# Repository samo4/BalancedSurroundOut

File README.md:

# BalancedSurroundOut

I2S balanced +4dBu DAC.

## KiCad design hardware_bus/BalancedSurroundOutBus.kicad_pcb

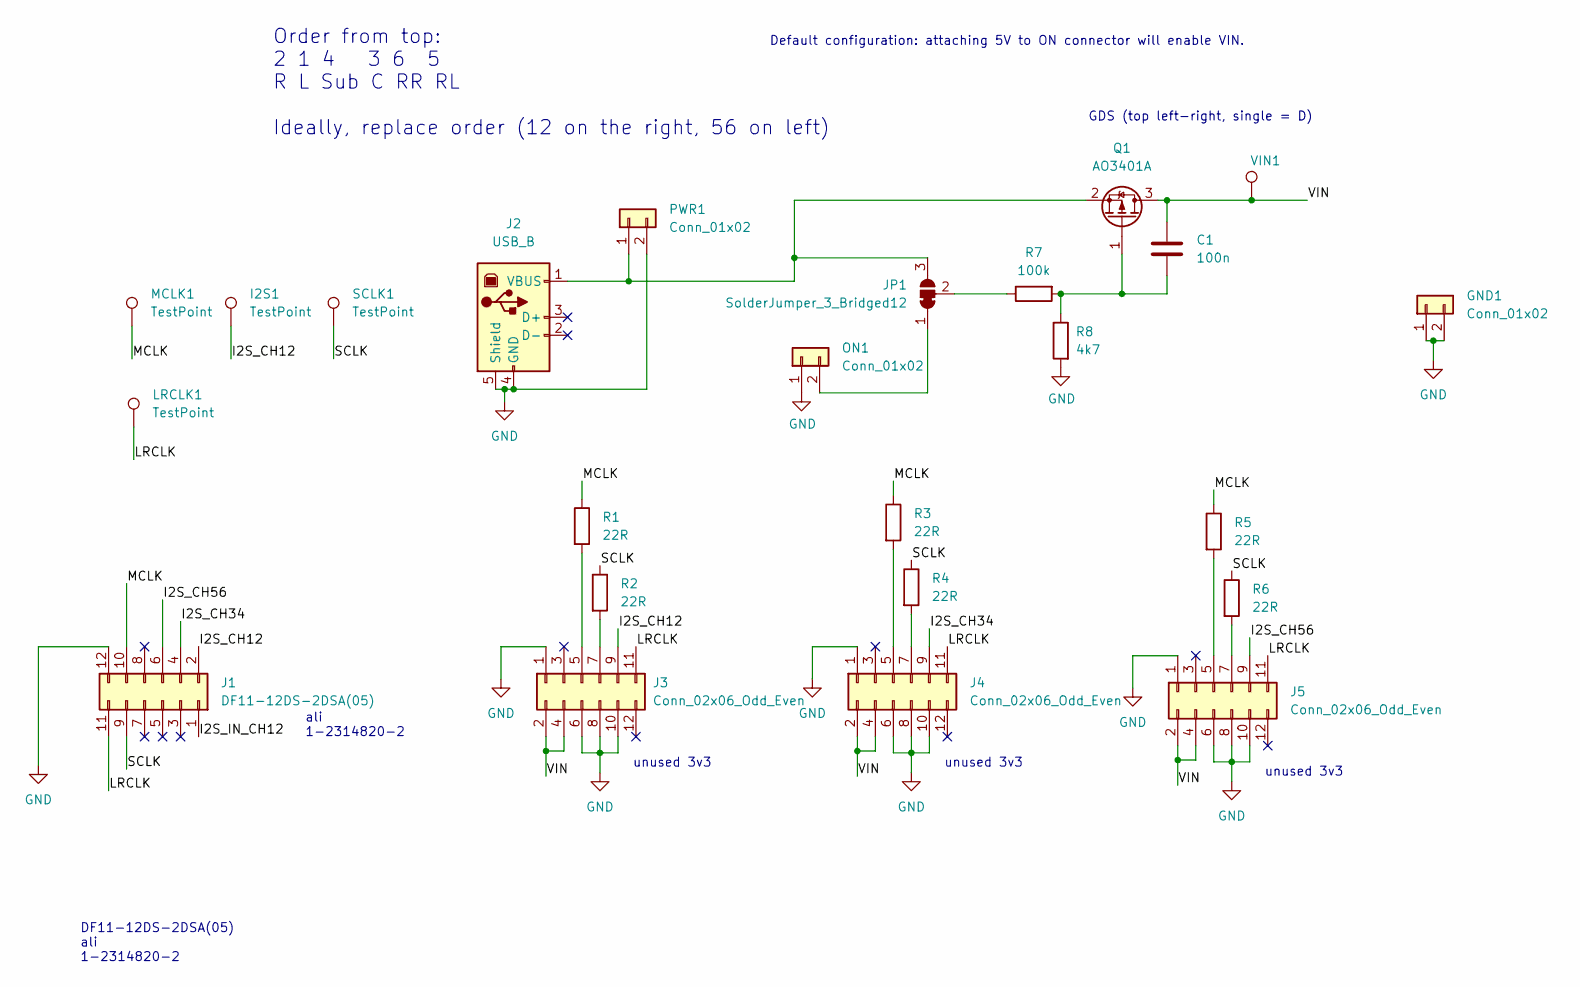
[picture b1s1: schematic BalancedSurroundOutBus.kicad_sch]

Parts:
C1: 100n; C_0402_1005Metric; LCSC C307331
GND1: Conn_01x02; PinHeader_1x02_P2.54mm_Vertical
I2S1: TestPoint; TestPoint_Pad_D1.0mm
J1: DF11-12DS-2DSA(05); PinHeader_2x06_P2.00mm_Vertical
J2: USB_B; USB_B_Lumberg_2411_02_Horizontal
J3, J4, J5: Conn_02x06_Odd_Even; PinHeader_2x06_P2.54mm_Vertical
JP1: SolderJumper_3_Bridged12; SolderJumper-3_P1.3mm_Bridged2Bar12_Pad1.0x1.5mm
LRCLK1: TestPoint; TestPoint_Pad_D1.0mm
MCLK1: TestPoint; TestPoint_Pad_D1.0mm
ON1: Conn_01x02; PinHeader_1x02_P2.54mm_Vertical
PWR1: Conn_01x02; PinHeader_1x02_P2.54mm_Vertical
Q1: AO3401A; SOT-23
R1, R2, R3, R4, R5, R6: 22R; R_0402_1005Metric_Pad0.72x0.64mm_HandSolder
R7: 100k; R_0402_1005Metric
R8: 4k7; R_0402_1005Metric; LCSC C25900
SCLK1: TestPoint; TestPoint_Pad_D1.0mm
VIN1: TestPoint; TestPoint_Pad_D1.0mm

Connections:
/I2S_CH12: I2S1.1, J1.2, J3.9
/I2S_CH34: J1.4, J4.9
/I2S_CH56: J1.6, J5.9
/I2S_IN_CH12: J1.1
/LRCLK: J1.11, J3.11, J4.11, J5.11, LRCLK1.1
/MCLK: J1.10, MCLK1.1, R1.1, R3.1, R5.1
/SCLK: J1.9, R2.1, R4.1, R6.1, SCLK1.1
/VIN: C1.1, J3.2, J3.4, J4.2, J4.4, J5.2, J5.4, Q1.3 (D), VIN1.1
GND: GND1.1, GND1.2, J1.12, J2.4 (GND), J2.5 (Shield), J3.1, J3.6, J3.8, J3.10, J4.1, J4.6, J4.8, J4.10, J5.1, J5.6, J5.8, J5.10, ON1.1, PWR1.2, R8.2
unnamed: J2.1 (VBUS), JP1.3 (B), PWR1.1, Q1.2 (S)
unnamed: J3.5, R1.2
unnamed: J3.7, R2.2
unnamed: J4.5, R3.2
unnamed: J4.7, R4.2
unnamed: J5.5, R5.2
unnamed: J5.7, R6.2
unnamed: JP1.1 (A), ON1.2
unnamed: JP1.2 (C), R7.1
unnamed: C1.2, Q1.1 (G), R7.2, R8.1

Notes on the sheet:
unused 3v3
Default configuration: attaching 5V to ON connector will enable VIN.
DF11-12DS-2DSA(05) ali 1-2314820-2
GDS (top left-right, single = D)
Order from top: 2 1 4 3 6 5 R L Sub C RR RL Ideally, replace order (12 on the right, 56 on left)
ali 1-2314820-2

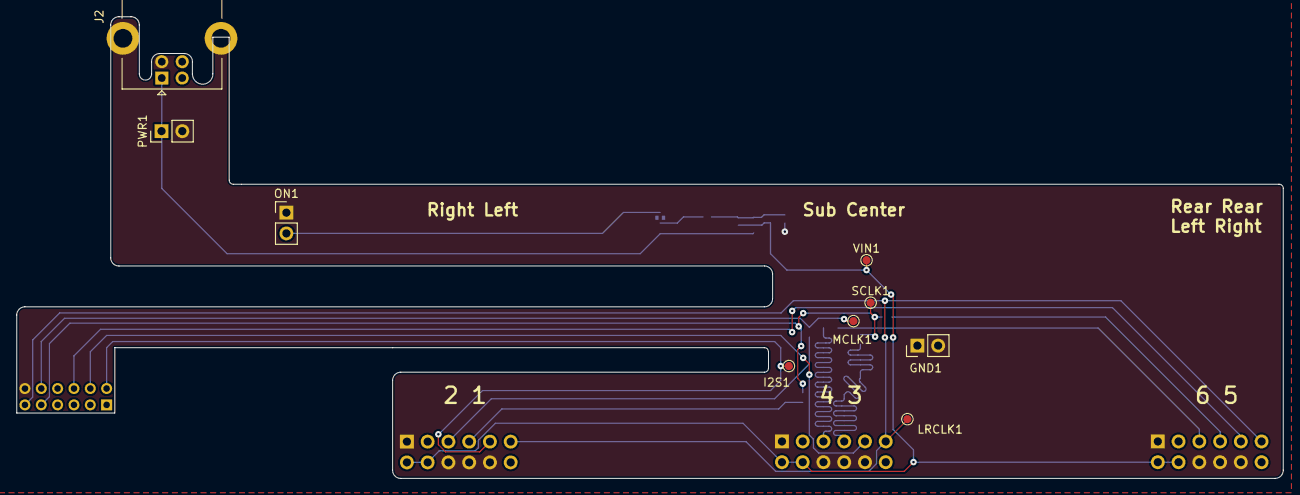
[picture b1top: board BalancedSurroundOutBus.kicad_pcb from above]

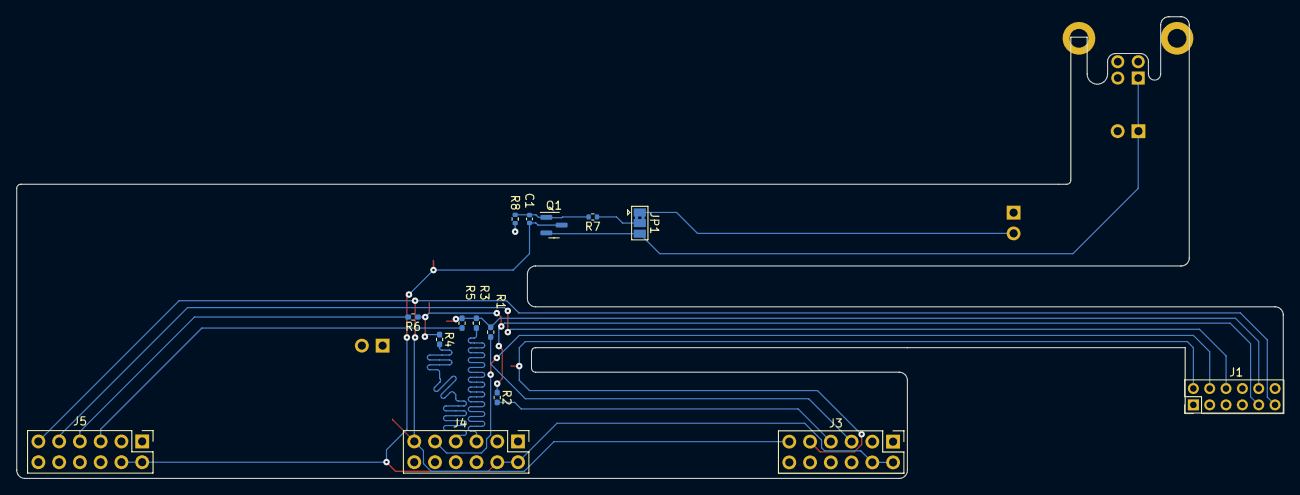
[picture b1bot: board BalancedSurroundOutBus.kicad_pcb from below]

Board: 2 copper layers, 155.0 x 56.5 mm, 24 parts (15 on the bottom side), 18 nets.

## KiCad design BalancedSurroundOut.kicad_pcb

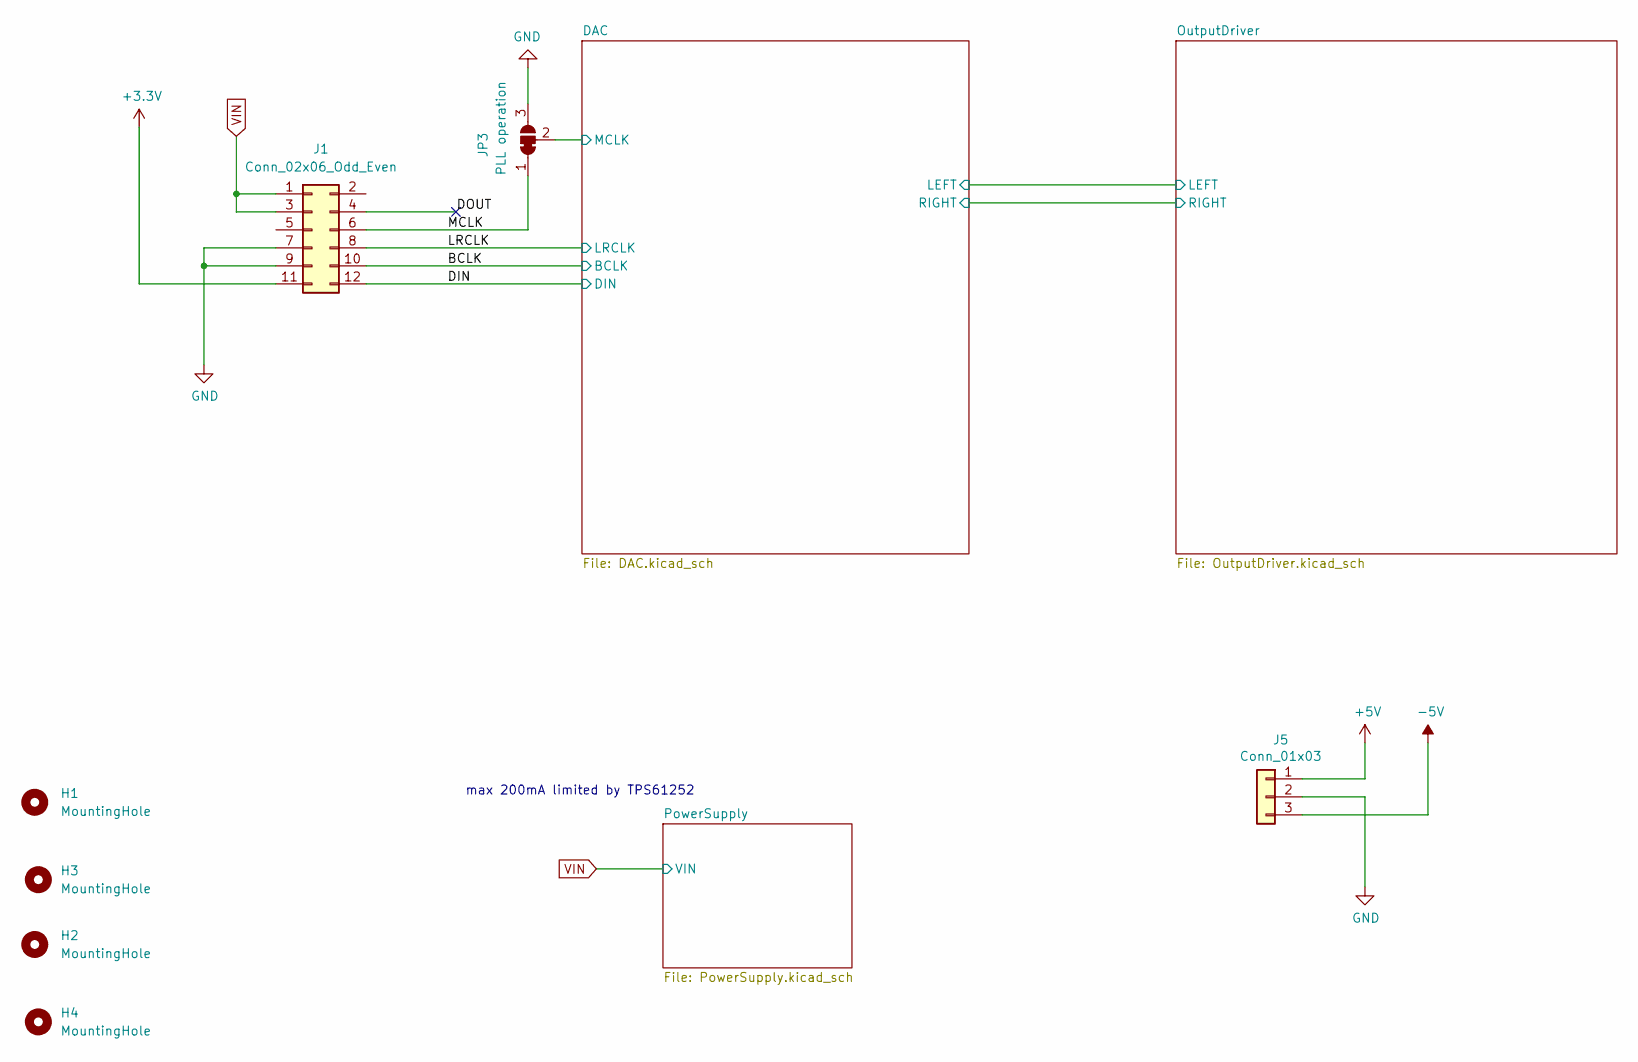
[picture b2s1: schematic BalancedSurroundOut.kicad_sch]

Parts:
H1, H2, H3, H4: MountingHole; MountingHole_3.2mm_M3
J1: Conn_02x06_Odd_Even; PinHeader_2x06_P2.54mm_Vertical
J5: Conn_01x03; PinHeader_1x03_P2.54mm_Vertical
JP3: PLL operation; SolderJumper-3_P1.3mm_Bridged12_Pad1.0x1.5mm

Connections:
+3V3: J1.11; also elsewhere on the board
+5V: J5.1; also elsewhere on the board
-5V: J5.3; also elsewhere on the board
/DAC/BCLK: J1.8; also elsewhere on the board
/DAC/DIN: J1.10; also elsewhere on the board
/DAC/LRCLK: J1.12; also elsewhere on the board
/DOUT: J1.4
/MCLK: J1.6, JP3.1 (A); also elsewhere on the board
GND: J1.2, J1.5, J1.7, J1.9, J5.2, JP3.3 (B); also elsewhere on the board
VIN: J1.1, J1.3; also elsewhere on the board

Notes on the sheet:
max 200mA limited by TPS61252

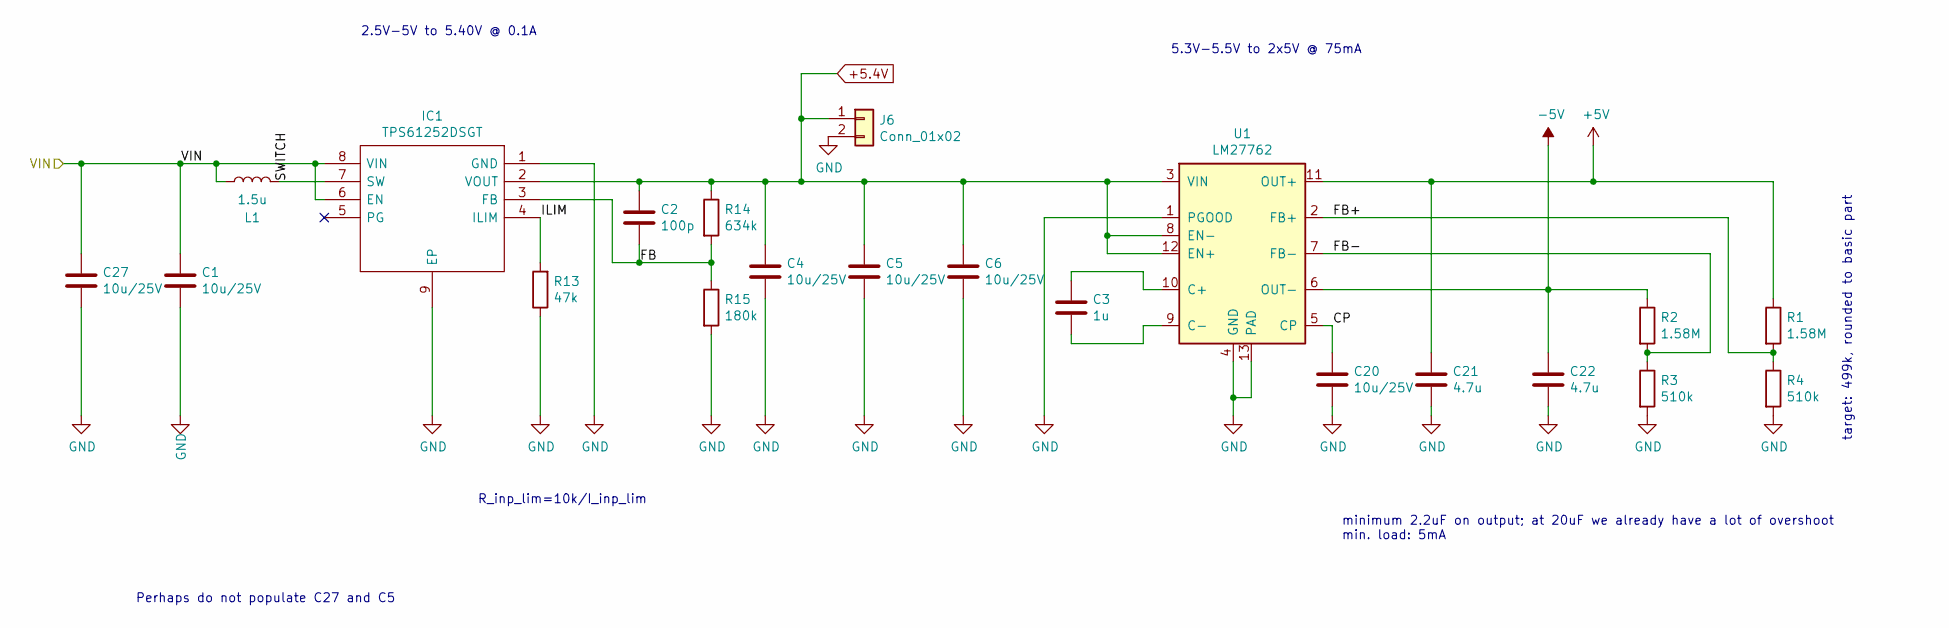
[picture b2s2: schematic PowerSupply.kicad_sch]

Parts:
C1, C4, C5, C6, C20, C27: 10u/25V; C_0805_2012Metric
C2: 100p; C_0603_1608Metric
C3: 1u; C_0402_1005Metric
C21, C22: 4.7u; C_0603_1608Metric
IC1: TPS61252DSGT; SON50P200X200X80-9N; Manufacturer_Part_Number TPS61252DSGT; Mouser Part Number 595-TPS61252DSGT
J6: Conn_01x02; PinHeader_1x02_P2.54mm_Vertical
L1: 1.5u; SRN30151R5Y
R1, R2: 1.58M; R_0402_1005Metric; LCSC C477217
R3, R4: 510k; R_0402_1005Metric; LCSC C11616
R13: 47k; R_0402_1005Metric
R14: 634k; R_0402_1005Metric; LCSC C228942
R15: 180k; R_0402_1005Metric; LCSC C25760
U1: LM27762; WSON-12-1EP_3x2mm_P0.5mm_EP1x2.65_ThermalVias

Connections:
+5.4V: C2.1, C4.1, C5.1, C6.1, IC1.2 (VOUT), J6.1, R14.1, U1.3 (VIN), U1.8 (EN-), U1.12 (EN+); also elsewhere on the board
+5V: C21.1, R1.1, U1.11 (OUT+); also elsewhere on the board
-5V: C22.1, R2.1, U1.6 (OUT-); also elsewhere on the board
/PowerSupply/CP: C20.1, U1.5 (CP)
/PowerSupply/FB: C2.2, IC1.3 (FB), R14.2, R15.1
/PowerSupply/FB+: R1.2, R4.1, U1.2 (FB+)
/PowerSupply/FB-: R2.2, R3.1, U1.7 (FB-)
/PowerSupply/ILIM: IC1.4 (ILIM), R13.2
/PowerSupply/SWITCH: IC1.7 (SW), L1.2
GND: C1.2, C4.2, C5.2, C6.2, C20.2, C21.2, C22.2, C27.2, IC1.1 (GND), IC1.9 (EP), J6.2, R3.2, R4.2, R13.1, R15.2, U1.1 (PGOOD), U1.4 (GND), U1.13 (PAD); also elsewhere on the board
unnamed: C3.1, U1.10 (C+)
unnamed: C3.2, U1.9 (C-)
VIN: C1.1, C27.1, IC1.6 (EN), IC1.8 (VIN), L1.1; also elsewhere on the board

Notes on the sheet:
5.3V-5.5V to 2x5V @ 75mA
R_inp_lim=10k/I_inp_lim
Perhaps do not populate C27 and C5
2.5V-5V to 5.40V @ 0.1A
target: 499k, rounded to basic part
minimum 2.2uF on output; at 20uF we already have a lot of overshoot min. load: 5mA

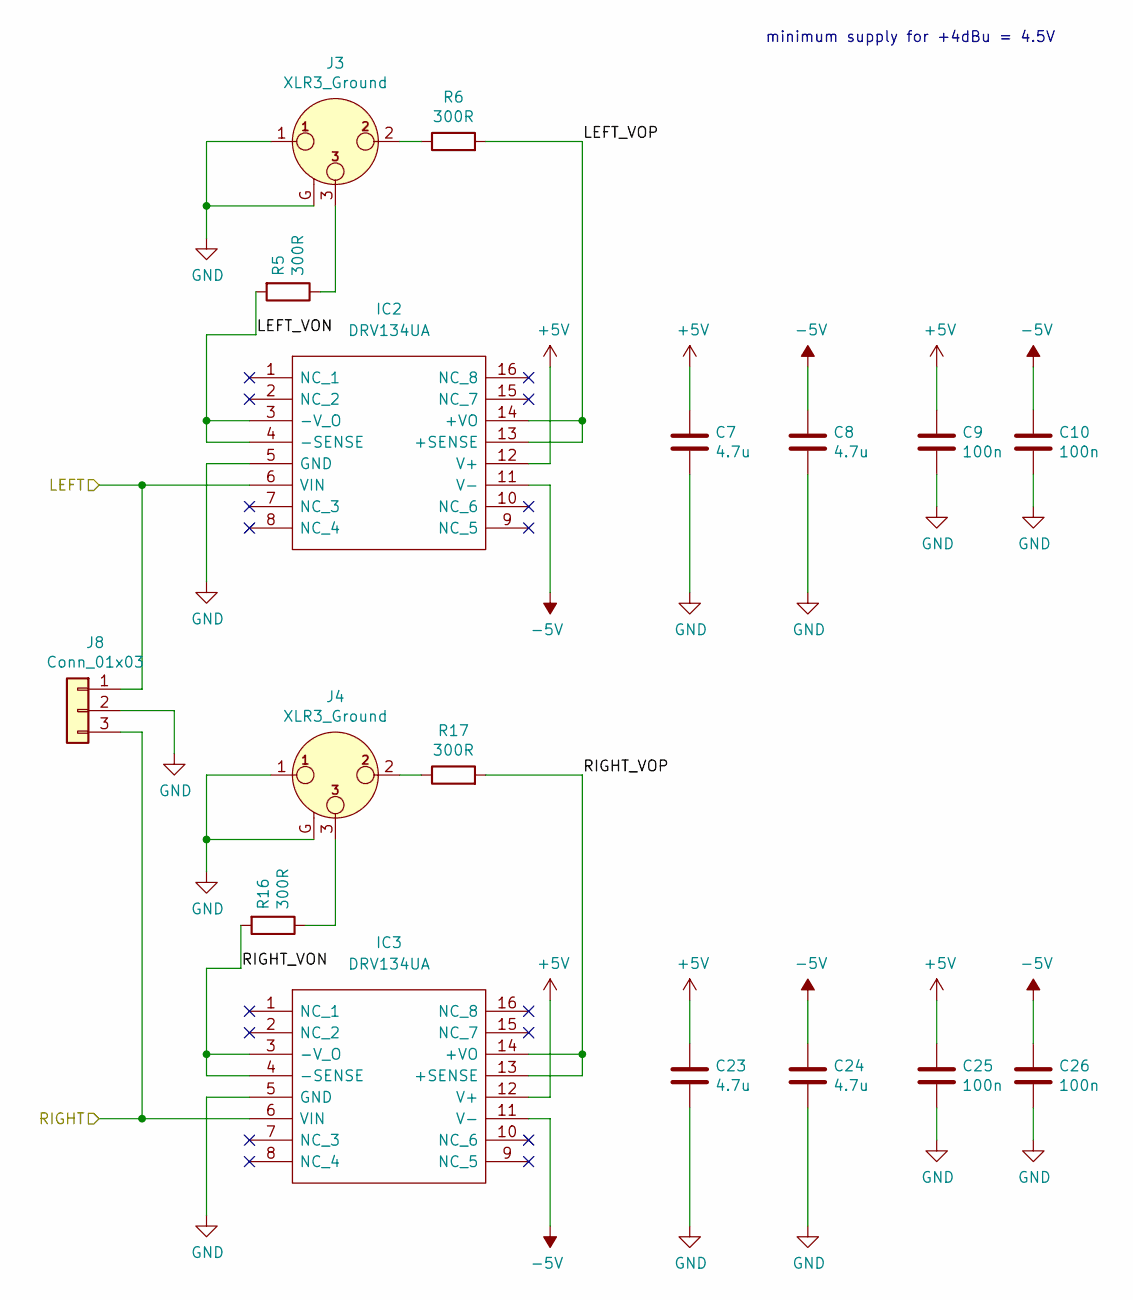
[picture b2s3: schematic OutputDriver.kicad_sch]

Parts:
C7, C8, C23, C24: 4.7u; C_0603_1608Metric
C9, C10, C25, C26: 100n; C_0402_1005Metric
IC2, IC3: DRV134UA; SOIC127P1030X265-16N; Manufacturer_Part_Number DRV134UA; Mouser Part Number 595-DRV134UA
J3, J4: XLR3_Ground; XLR-NC3MA
J8: Conn_01x03; PinHeader_1x03_P2.54mm_Vertical
R5, R6, R16, R17: 300R; R_0603_1608Metric

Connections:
+5V: C7.1, C9.1, C23.1, C25.1, IC2.12 (V+), IC3.12 (V+); also elsewhere on the board
-5V: C8.1, C10.1, C24.1, C26.1, IC2.11 (V-), IC3.11 (V-); also elsewhere on the board
/DAC/LEFT: IC2.6 (VIN), J8.1; also elsewhere on the board
/DAC/RIGHT: IC3.6 (VIN), J8.3; also elsewhere on the board
/OutputDriver/LEFT_VON: IC2.3 (-V_O), IC2.4 (-SENSE), R5.2
/OutputDriver/LEFT_VOP: IC2.13 (+SENSE), IC2.14 (+VO), R6.2
/OutputDriver/RIGHT_VON: IC3.3 (-V_O), IC3.4 (-SENSE), R16.2
/OutputDriver/RIGHT_VOP: IC3.13 (+SENSE), IC3.14 (+VO), R17.2
GND: C7.2, C8.2, C9.2, C10.2, C23.2, C24.2, C25.2, C26.2, IC2.5 (GND), IC3.5 (GND), J3.1, J3.G, J4.1, J4.G, J8.2; also elsewhere on the board
unnamed: J3.2, R6.1
unnamed: J3.3, R5.1
unnamed: J4.2, R17.1
unnamed: J4.3, R16.1

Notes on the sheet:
minimum supply for +4dBu = 4.5V

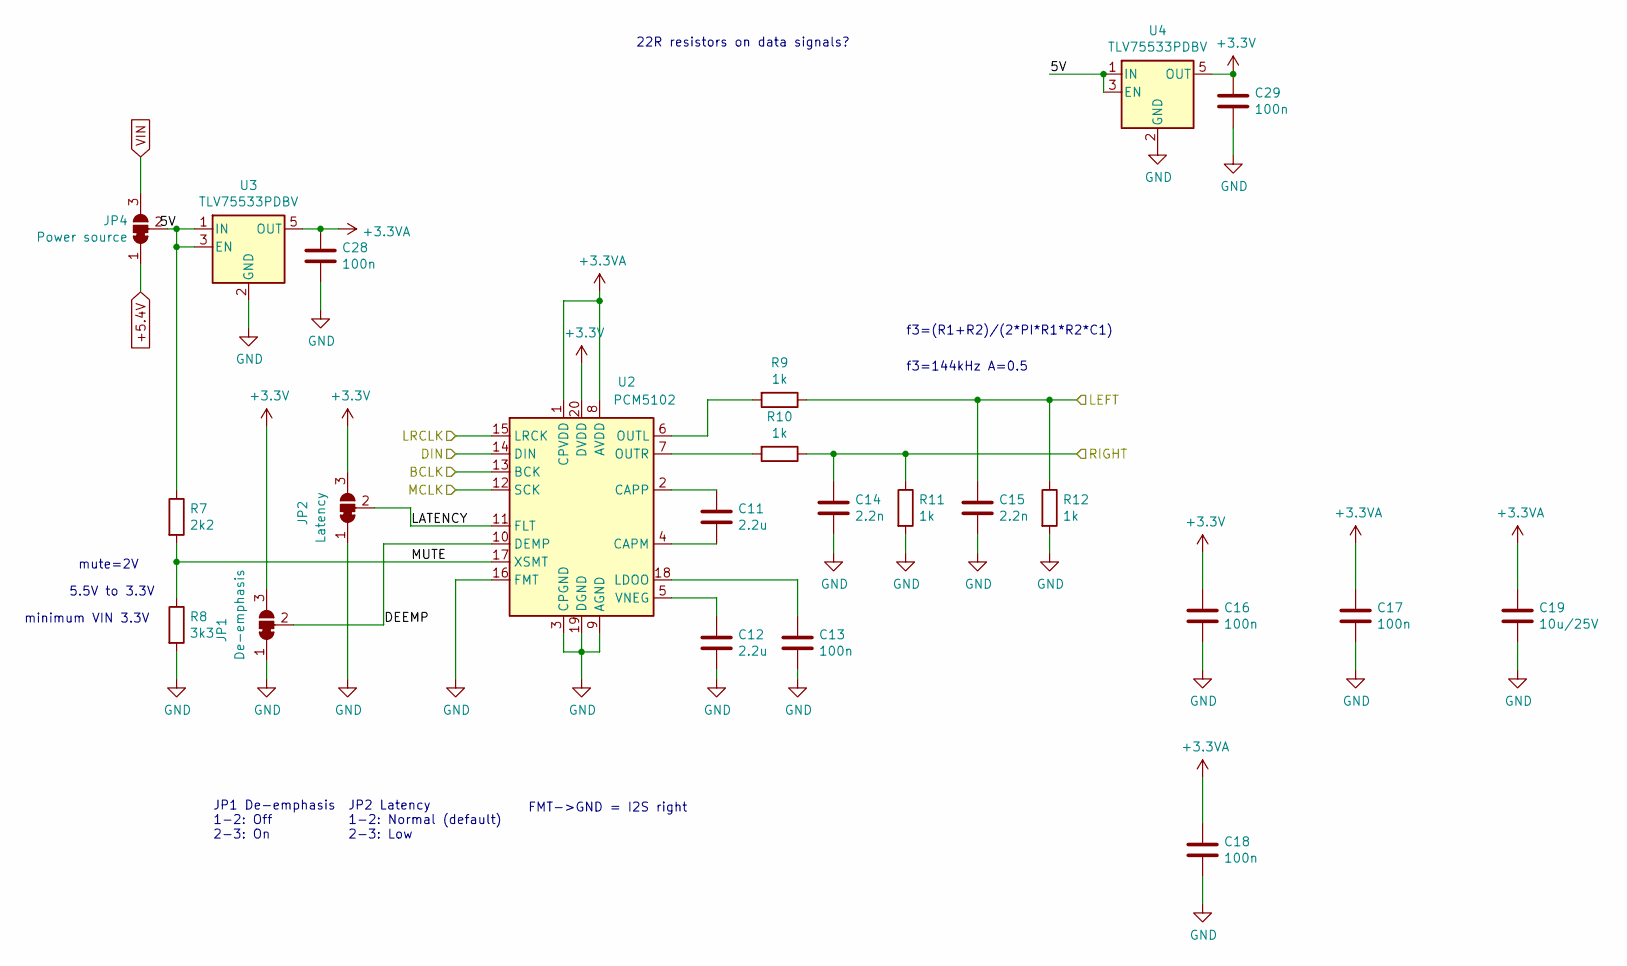
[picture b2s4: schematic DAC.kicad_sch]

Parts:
C11, C12: 2.2u; C_0805_2012Metric; LCSC C49217
C13: 100n; C_0402_1005Metric
C14, C15: 2.2n; C_0402_1005Metric
C16, C17, C18, C28, C29: 100n; C_0402_1005Metric; LCSC C307331
C19: 10u/25V; C_0805_2012Metric
JP1: De-emphasis; SolderJumper-3_P1.3mm_Bridged12_Pad1.0x1.5mm
JP2: Latency; SolderJumper-3_P1.3mm_Bridged12_Pad1.0x1.5mm
JP4: Power source; SolderJumper-3_P1.3mm_Bridged12_Pad1.0x1.5mm
R7: 2k2; R_0402_1005Metric
R8: 3k3; R_0402_1005Metric
R9, R10, R11, R12: 1k; R_0402_1005Metric
U2: PCM5102; TSSOP-20_4.4x6.5mm_P0.65mm
U3, U4: TLV75533PDBV; SOT-23-5

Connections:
+3.3VA: C17.1, C18.1, C19.1, C28.1, U2.1 (CPVDD), U2.8 (AVDD), U3.5 (OUT)
+3V3: C16.1, C29.1, JP1.3 (B), JP2.3 (B), U2.20 (DVDD), U4.5 (OUT); also elsewhere on the board
+5.4V: JP4.1 (A); also elsewhere on the board
/DAC/5V: JP4.2 (C), R7.1, U3.1 (IN), U3.3 (EN), U4.1 (IN), U4.3 (EN)
/DAC/BCLK: U2.13 (BCK); also elsewhere on the board
/DAC/DEEMP: JP1.2 (C), U2.10 (DEMP)
/DAC/DIN: U2.14 (DIN); also elsewhere on the board
/DAC/LATENCY: JP2.2 (C), U2.11 (FLT)
/DAC/LEFT: C15.1, R9.1, R12.1; also elsewhere on the board
/DAC/LRCLK: U2.15 (LRCK); also elsewhere on the board
/DAC/MCLK: U2.12 (SCK); also elsewhere on the board
/DAC/MUTE: R7.2, R8.1, U2.17 (XSMT)
/DAC/RIGHT: C14.1, R10.1, R11.1; also elsewhere on the board
GND: C12.2, C13.2, C14.2, C15.2, C16.2, C17.2, C18.2, C19.2, C28.2, C29.2, JP1.1 (A), JP2.1 (A), R8.2, R11.2, R12.2, U2.3 (CPGND), U2.9 (AGND), U2.16 (FMT), U2.19 (DGND), U3.2 (GND), U4.2 (GND); also elsewhere on the board
unnamed: C11.1, U2.2 (CAPP)
unnamed: C11.2, U2.4 (CAPM)
unnamed: C12.1, U2.5 (VNEG)
unnamed: C13.1, U2.18 (LDOO)
unnamed: R9.2, U2.6 (OUTL)
unnamed: R10.2, U2.7 (OUTR)
VIN: JP4.3 (B); also elsewhere on the board

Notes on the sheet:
minimum VIN 3.3V
f3=144kHz A=0.5
mute=2V
JP1 De-emphasis 1-2: Off 2-3: On
5.5V to 3.3V
FMT->GND = I2S right
JP2 Latency 1-2: Normal (default) 2-3: Low
22R resistors on data signals?
f3=(R1+R2)/(2*PI*R1*R2*C1)

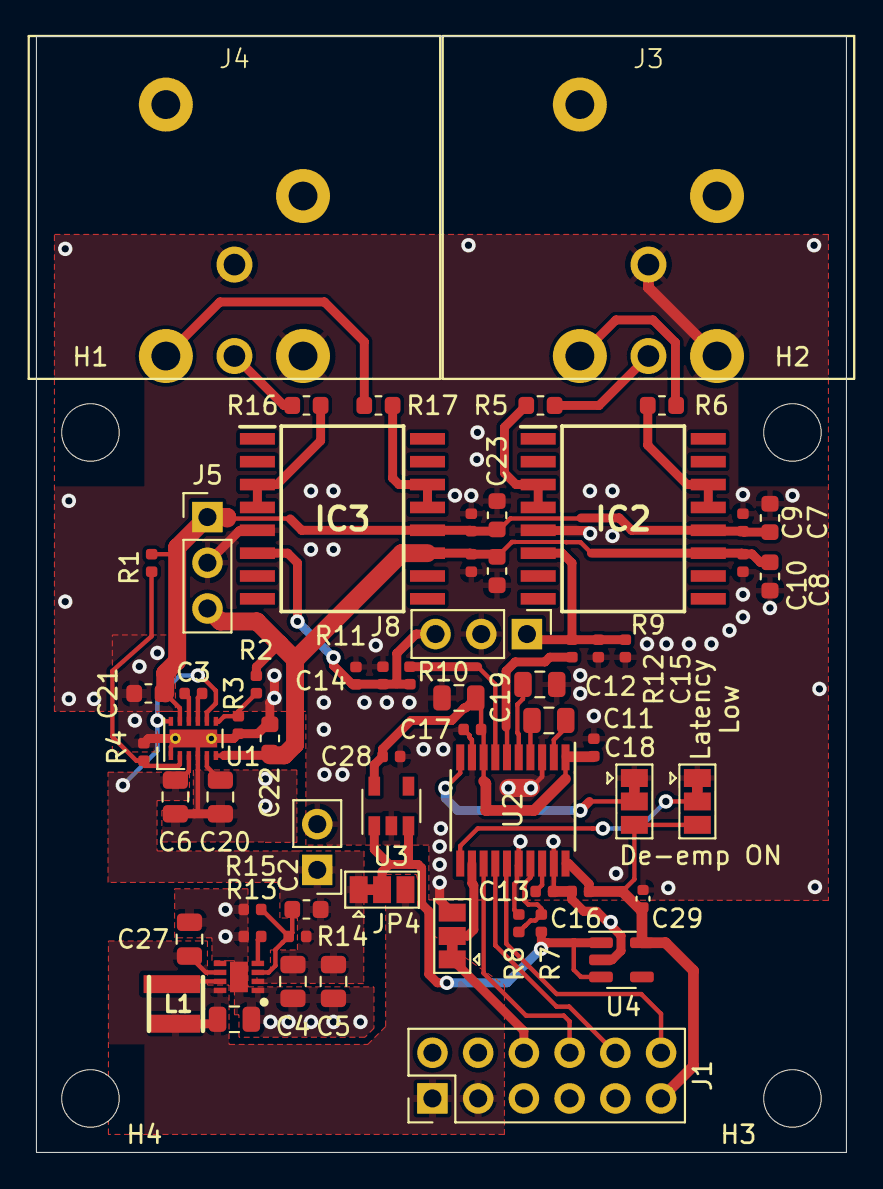
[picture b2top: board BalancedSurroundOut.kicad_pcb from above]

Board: 2 copper layers, 45.0 x 62.0 mm, 68 parts (0 on the bottom side), 40 nets.

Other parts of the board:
locked: PLL operation; SolderJumper-3_P1.3mm_Bridged12_Pad1.0x1.5mm

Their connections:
/DAC/MCLK: locked.2 (C); also elsewhere on the board
/MCLK: locked.1 (A); also elsewhere on the board
GND: locked.3 (B); also elsewhere on the board

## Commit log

2022-09-24 import
2022-09-24 cleanup
2022-09-25 refactor
2022-09-25 removed autosave
2022-09-25 latest
2022-10-01 ready for JLCPCB
2022-10-04 smth
2023-03-19 joining

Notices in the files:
README.md:
License: BSD 3-Clause
